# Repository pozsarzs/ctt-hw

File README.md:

**CTT - transistor tester and characteristic curve plotter**  
Copyright (C) 2010-2022 Pozsár Zsolt <pozsarzs@gmail.com>  
Homepage: <http://www.pozsarzs.hu/>  
GitHub: <https://github.com/pozsarzs/ctt-hw>

**Documentation**

- version:             1.0
- language:            en
- licence:             CC-BY-NC-4.0

**Hardware**

 - version:            v120128

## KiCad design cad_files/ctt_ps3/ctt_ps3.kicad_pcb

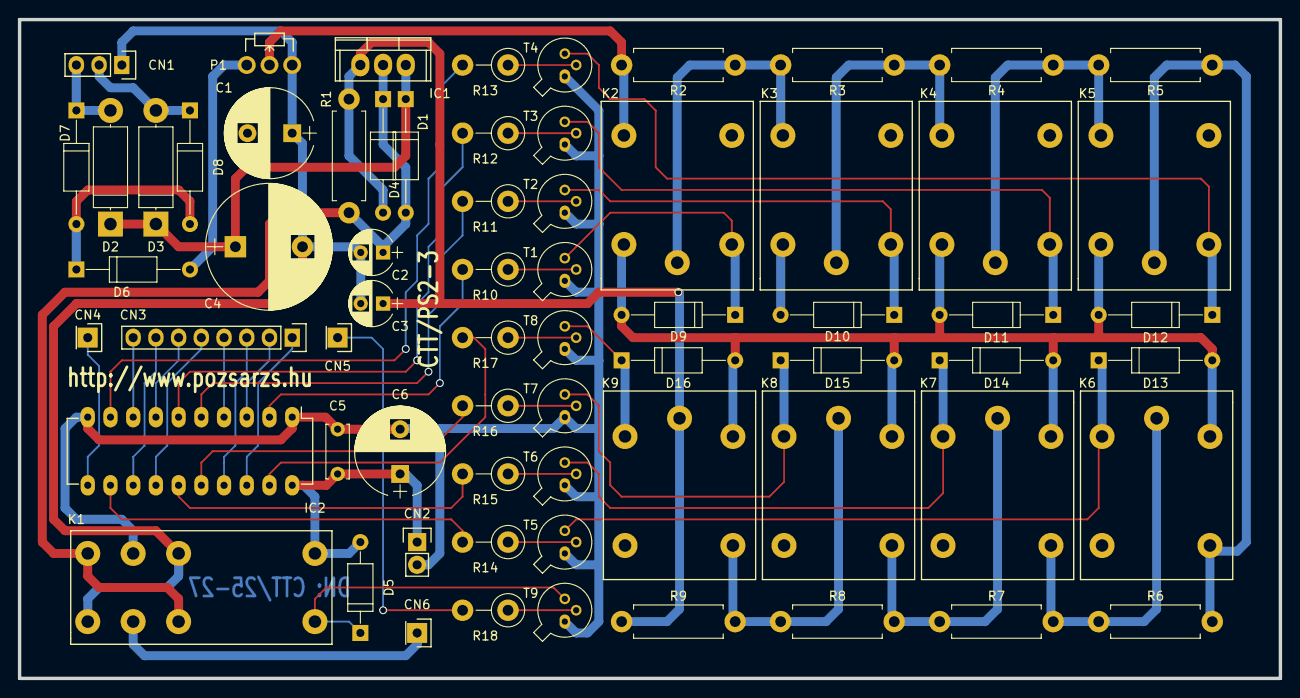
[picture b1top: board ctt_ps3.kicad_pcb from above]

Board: 2 copper layers, 141.0 x 73.7 mm, 67 parts (0 on the bottom side), 43 nets.

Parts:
C1: 2200u; CP_Radial_D14.0mm_P7.50mm
C2, C3: 10u; CP_Radial_D5.0mm_P2.50mm
C4: 470u; CP_Radial_D10.0mm_P5.00mm
C5: 100u; CP_Radial_D10.0mm_P5.00mm
C6: 100n; C_Disc_D6.0mm_W2.5mm_P5.00mm
CN1: Pin_Header_Straight_1x03
CN2: Pin_Header_Straight_1x02
CN3: Pin_Header_Straight_1x08
CN4, CN5, CN6: Pin_Header_Straight_1x01
D1, D4: 1N4002; D_A-405_P12.70mm_Horizontal
D2, D3: BY399; D_5W_P12.70mm_Horizontal
D5: 1N4001; D_A-405_P10.16mm_Horizontal
D6: ZPD27; D_A-405_P12.70mm_Horizontal
D7, D8, D9, D10, D11, D12, D13, D14, D15, D16: 1N4001; D_A-405_P12.70mm_Horizontal
IC1: LM317L; TO-220
IC2: 74LS374; DIP-20_W7.62mm_LongPads
K1: LMR2-5D; relay_lmr2
K2, K3, K4, K5, K6, K7, K8, K9: LEG-5; relay_leg
P1: 390; Potentiometer_WirePads_Small
R1: 640; R_Axial_DIN0411_L9.9mm_D3.6mm_P12.70mm_Horizontal
R2: 2; R_Axial_DIN0411_L9.9mm_D3.6mm_P12.70mm_Horizontal
R3: 4; R_Axial_DIN0411_L9.9mm_D3.6mm_P12.70mm_Horizontal
R4: 8; R_Axial_DIN0411_L9.9mm_D3.6mm_P12.70mm_Horizontal
R5: 16; R_Axial_DIN0411_L9.9mm_D3.6mm_P12.70mm_Horizontal
R6: 32; R_Axial_DIN0411_L9.9mm_D3.6mm_P12.70mm_Horizontal
R7: 64; R_Axial_DIN0411_L9.9mm_D3.6mm_P12.70mm_Horizontal
R8: 128; R_Axial_DIN0411_L9.9mm_D3.6mm_P12.70mm_Horizontal
R9: 256; R_Axial_DIN0411_L9.9mm_D3.6mm_P12.70mm_Horizontal
R10, R11, R12, R13, R14, R15, R16, R17, R18: 1k; R_Axial_DIN0411_L9.9mm_D3.6mm_P5.08mm_Vertical
T1, T2, T3, T4, T5, T6, T7, T8, T9: BC109; TO-18-3

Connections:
/5V 100mA AC: D2.2, D3.2, D7.1, D8.1
/5V 100mA AC COM: C1.2, C2.2, C3.2, C4.1, K1.3, K1.6, P1.1
GND: C5.2, C6.2, IC2.1, IC2.10, K1.4, T1.1, T2.1, T3.1, T4.1, T5.1, T6.1, T7.1, T8.1, T9.1
unnamed: C1.1, D1.1, D2.1, D3.1, IC1.3
unnamed: C2.1, D1.2, D4.1, IC1.2, K1.5, K1.8, R1.1
unnamed: C3.1, D4.2, IC1.1, K9.3, R1.2, R9.1
unnamed: C4.2, D6.1, D7.2, D8.2
unnamed: D5.2, K1.2, T9.3
unnamed: D6.2, P1.3
unnamed: D9.2, K2.2, T1.3
unnamed: D10.2, K3.2, T2.3
unnamed: D11.2, K4.2, T3.3
unnamed: D12.2, K5.2, T4.3
unnamed: D13.2, K6.2, T5.3
unnamed: D14.2, K7.2, T6.3
unnamed: D15.2, K8.2, T7.3
unnamed: D16.2, K9.2, T8.3
unnamed: IC2.2, R10.2
unnamed: IC2.5, R11.2
unnamed: IC2.6, R12.2
unnamed: IC2.9, R13.2
unnamed: IC2.12, R14.2
unnamed: IC2.15, R15.2
unnamed: IC2.16, R16.2
unnamed: IC2.19, R17.2
unnamed: K2.3, K3.4, R2.1, R3.2
unnamed: K2.4, P1.2, R2.2
unnamed: K3.3, K4.4, R3.1, R4.2
unnamed: K4.3, K5.4, R4.1, R5.2
unnamed: K5.3, K6.4, R5.1, R6.2
unnamed: K6.3, K7.4, R6.1, R7.2
unnamed: K7.3, K8.4, R7.1, R8.2
unnamed: K8.3, K9.4, R8.1, R9.2
unnamed: R10.1, T1.2
unnamed: R11.1, T2.2
unnamed: R12.1, T3.2
unnamed: R13.1, T4.2
unnamed: R14.1, T5.2
unnamed: R15.1, T6.2
unnamed: R16.1, T7.2
unnamed: R17.1, T8.2
unnamed: R18.1, T9.2
VCC: C5.1, C6.1, D5.1, D9.1, D10.1, D11.1, D12.1, D13.1, D14.1, D15.1, D16.1, IC2.20, K1.1, K2.1, K3.1, K4.1, K5.1, K6.1, K7.1, K8.1, K9.1

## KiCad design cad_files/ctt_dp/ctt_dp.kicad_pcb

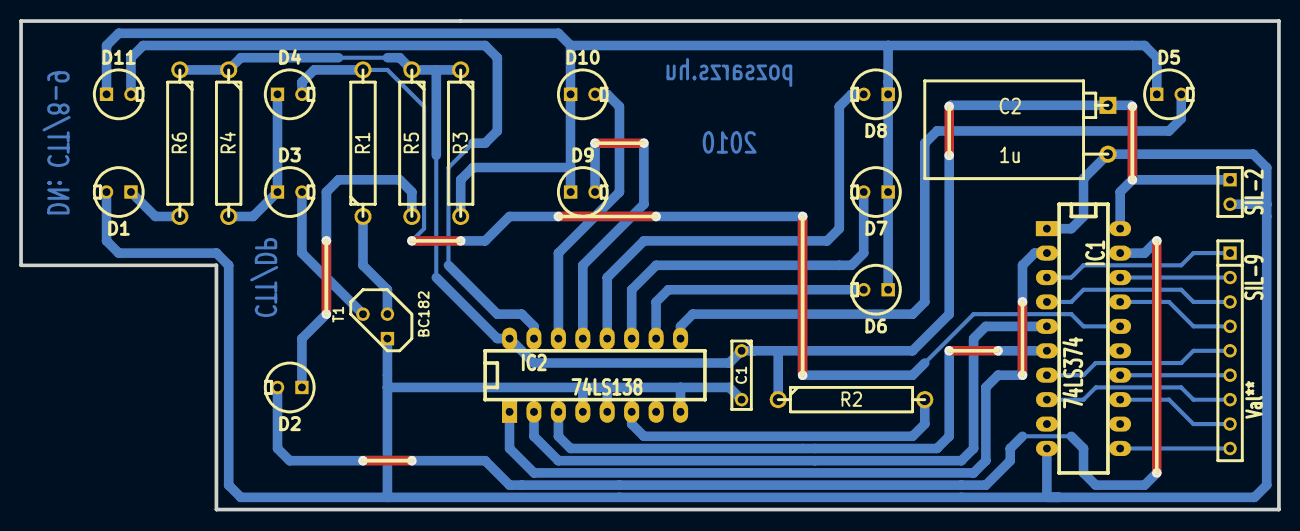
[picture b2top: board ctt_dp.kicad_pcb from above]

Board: 2 copper layers, 130.8 x 50.8 mm, 24 parts (0 on the bottom side), 21 nets.

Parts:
C1: 33n; C2
C2: 1u; CPR10X16
D1, D2, D3, D4, D5, D6, D7, D8, D9, D10, D11: LED; LEDV
IC1: 74LS374; 20DIP-ELL300
IC2: 74LS138; 16DIP-ELL300
R1, R2: 1k; R6
R3, R4, R5, R6: 330; R6
SIL-2: Val**; SIL-2
SIL-9: Val**; SIL-9
T1: BC182; TO92

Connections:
+5V: C1.1, C2.1, IC1.20, IC2.16, R2.1, R3.1, R4.1, R5.1, R6.1
GND: C1.2, C2.2, D1.2, IC1.1, IC1.10, IC2.4, IC2.5, IC2.8, T1.1
unnamed: D1.1, R6.2
unnamed: IC2.6, R2.2
unnamed: R1.1, T1.2
unnamed: D4.2, IC1.16, R1.2
unnamed: D2.1, R5.2
unnamed: IC1.5, IC2.2
unnamed: D5.1, D6.1, D7.1, D8.1, D9.1, D10.1, D11.1, R3.2
unnamed: D6.2, IC2.10
unnamed: D8.2, IC2.12
unnamed: D10.2, IC2.14
unnamed: D11.2, IC2.15
unnamed: D9.2, IC2.13
unnamed: D7.2, IC2.11
unnamed: D5.2, IC2.9
unnamed: IC1.2, IC2.1
unnamed: IC1.6, IC2.3
unnamed: D3.1, D4.1, R4.2
unnamed: D3.2, T1.3
unnamed: D2.2, IC1.19

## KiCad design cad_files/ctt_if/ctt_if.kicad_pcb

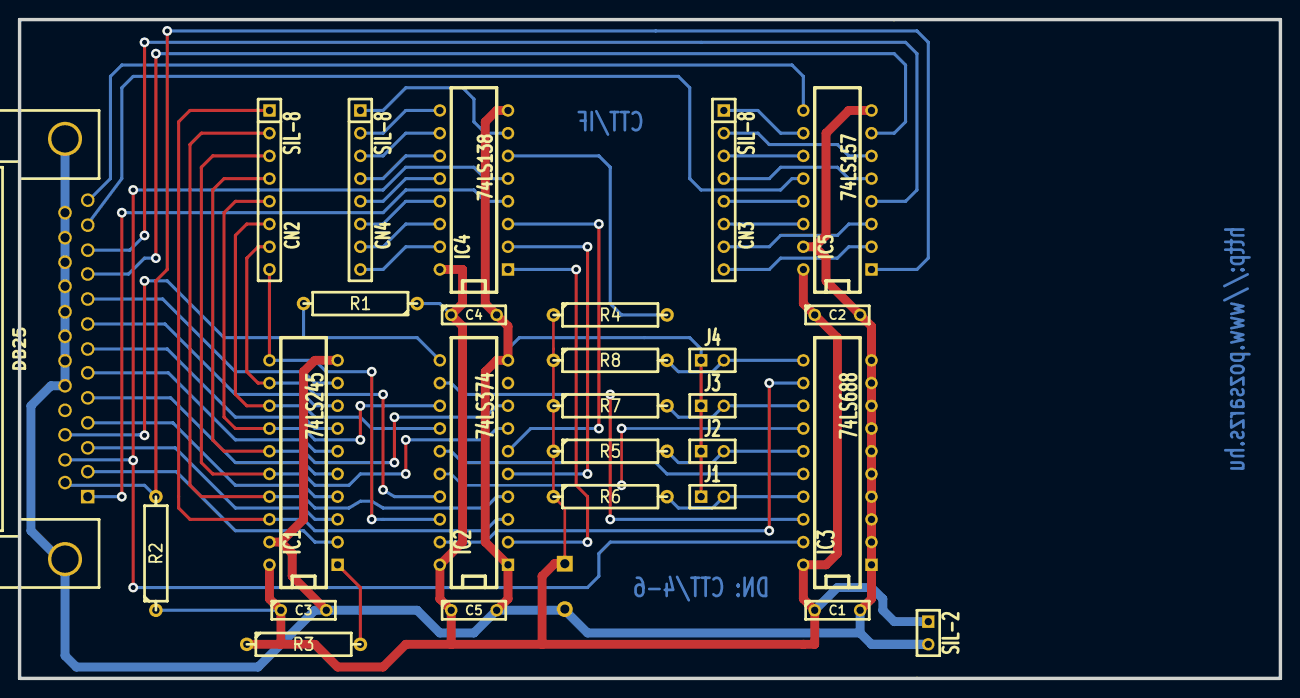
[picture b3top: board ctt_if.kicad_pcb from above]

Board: 2 copper layers, 141.0 x 73.7 mm, 28 parts (1 on the bottom side), 39 nets.

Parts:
C1, C2, C3, C4, C5: 33n; C2
C6: 100u; CPR10X16
CN1: DB25; DB25FC
IC1: 74LS245; 20dip300
IC2: 74LS374; 20dip300
IC3: 74LS688; 20dip300
IC4: 74LS138; 16dip300
IC5: 74LS157; 16dip300
J1, J2, J3, J4: JUMPER; SIL-2
R1, R2, R3, R4, R5, R6, R7, R8: 1k; R5
SIL-2: CN5; SIL-2
SIL-8: CN3; SIL-8
SIL-8#2: CN4; SIL-8
SIL-8#3: CN2; SIL-8

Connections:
/+5V: C1.1, C2.1, C3.1, C4.1, C5.1, C6.1, IC1.20, IC2.20, IC3.20, IC4.16, IC5.16, R1.1, R2.1, R3.1, R4.1, R5.1, R6.1, R7.1, R8.1
/DO0: IC1.18, IC2.3
/DO1: IC1.17, IC2.4
/DO2: IC1.16, IC2.7
/DO3: IC1.15, IC2.8
/DO4: IC1.14, IC2.13
/DO5: IC1.13, IC2.14
/DO6: IC1.12, IC2.17
/DO7: IC1.11, IC2.18
/GND: C1.2, C2.2, C3.2, C4.2, C5.2, C6.2, CN1.18, CN1.19, CN1.20, CN1.21, CN1.22, CN1.23, CN1.24, CN1.25, IC1.10, IC1.19, IC2.1, IC2.10, IC3.1, IC3.2, IC3.3, IC3.4, IC3.5, IC3.6, IC3.7, IC3.8, IC3.9, IC3.10, IC4.8, IC5.8, IC5.15, J1.1, J2.1, J3.1, J4.1
unnamed: IC3.11, J4.2, R8.2
unnamed: IC3.13, J3.2, R7.2
unnamed: IC3.15, J2.2, R5.2
unnamed: IC2.15, IC3.16
unnamed: IC2.19, IC3.12
unnamed: IC3.17, J1.2, R6.2
unnamed: CN1.1, IC4.4
unnamed: IC2.5, IC4.2
unnamed: CN1.2, IC1.2
unnamed: IC2.16, IC3.14
unnamed: IC2.12, IC3.18
unnamed: CN1.16, IC2.11, R1.2
unnamed: CN1.13, IC5.9
unnamed: CN1.14, IC5.1, R2.2
unnamed: CN1.15, IC3.19, IC4.5
unnamed: CN1.12, IC5.12
unnamed: IC1.1, R3.2
unnamed: CN1.11, IC5.4
unnamed: IC4.6, R4.2
unnamed: CN1.4, IC1.4
unnamed: CN1.6, IC1.6
unnamed: CN1.8, IC1.8
unnamed: IC2.6, IC4.3
unnamed: IC2.2, IC4.1
unnamed: CN1.10, IC5.7
unnamed: CN1.9, IC1.9
unnamed: CN1.7, IC1.7
unnamed: CN1.5, IC1.5
unnamed: CN1.3, IC1.3

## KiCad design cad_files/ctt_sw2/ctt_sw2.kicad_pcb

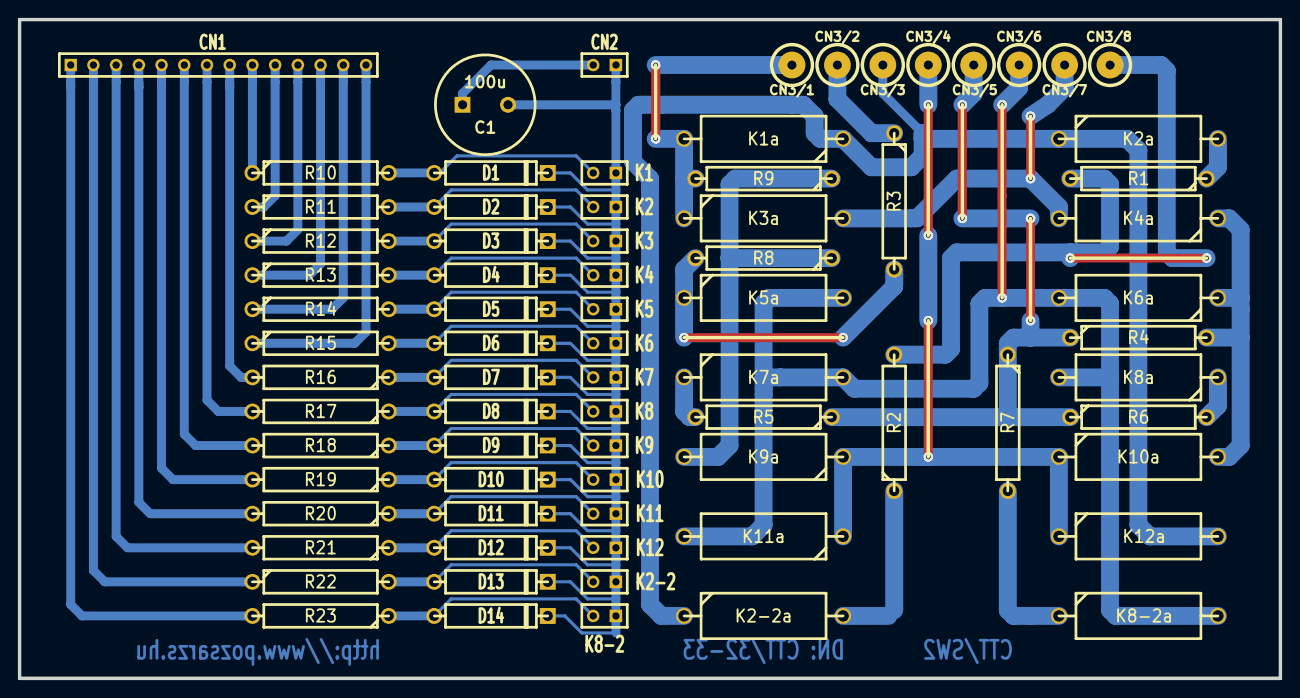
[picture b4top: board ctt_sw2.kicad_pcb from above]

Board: 2 copper layers, 141.0 x 73.7 mm, 76 parts (0 on the bottom side), 30 nets.

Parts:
1PIN: CN3/8; 1pin3
1PIN#2: CN3/7; 1pin3
1PIN#3: CN3/6; 1pin3
1PIN#4: CN3/1; 1pin3
1PIN#5: CN3/2; 1pin3
1PIN#6: CN3/3; 1pin3
1PIN#7: CN3/4; 1pin3
1PIN#8: CN3/5; 1pin3
C1: 100u; C2V10
D1, D2, D3, D4, D5, D6, D7, D8, D9, D10, D11, D12, D13, D14: 1N4148; D5
K1, K2, K2-2, K3, K4, K5, K6, K7, K8, K8-2, K9, K10, K11, K12: Reed_relay; SIL-2
K1a, K2-2a, K2a, K3a, K4a, K5a, K6a, K7a, K8-2a, K8a, K9a, K10a, K11a, K12a: SPST; R7
R1, R5: 100_1%; R6
R2, R10, R11, R12, R13, R14, R15, R16, R17, R18, R19, R20, R21, R22, R23: R; R6
R3: 33K; R6
R4: 1k_1%; R6
R6: 1_1%_1W; R6
R7: ?_1%_1W; R6
R8: 900K_1%; R6
R9: 100k_1%; R6
SIL-2: CN2; SIL-2
SIL-14: CN1; SIL-14

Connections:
0-1V_1: R1.2, R2.2
0-20V_1: R4.1, R5.1, R6.1, R7.1
+5V_1: C1.1, D1.2, D2.2, D3.2, D4.2, D5.2, D6.2, D7.2, D8.2, D9.2, D10.2, D11.2, D12.2, D13.2, D14.2, K1.1, K2.1, K2-2.1, K3.1, K4.1, K5.1, K6.1, K7.1, K8.1, K8-2.1, K9.1, K10.1, K11.1, K12.1
Base_1: K1a.1, K2-2a.1, K2a.1, K12a.2
COM_1: K1a.2, K3a.1, R9.2
Collector_1: K5a.2, K6a.2, K7a.2, K8-2a.2, K8a.2, K11a.2
Emitter_1: K3a.2, K4a.2
unnamed: D12.1, K12.2, R21.1
unnamed: D11.1, K11.2, R20.1
unnamed: D10.1, K10.2, R19.1
unnamed: D9.1, K9.2, R18.1
unnamed: D7.1, K7.2, R16.1
unnamed: D3.1, K3.2, R12.2
unnamed: D4.1, K4.2, R13.2
unnamed: D5.1, K5.2, R14.2
unnamed: D2.1, K2.2, R11.2
unnamed: K2-2a.2, R2.1
unnamed: K4a.1, K6a.1, K10a.2, R4.2
unnamed: K7a.1, R5.2
unnamed: K8-2a.1, R7.2
unnamed: K8a.1, R6.2
unnamed: K5a.1, R3.2, R8.2
unnamed: K2a.2, R1.1
unnamed: K9a.2, R8.1, R9.1
unnamed: D1.1, K1.2, R10.2
unnamed: D13.1, K2-2.2, R22.2
unnamed: D6.1, K6.2, R15.2
unnamed: D14.1, K8-2.2, R23.1
unnamed: D8.1, K8.2, R17.1
Um_1: K9a.1, K10a.1, K11a.1, K12a.1

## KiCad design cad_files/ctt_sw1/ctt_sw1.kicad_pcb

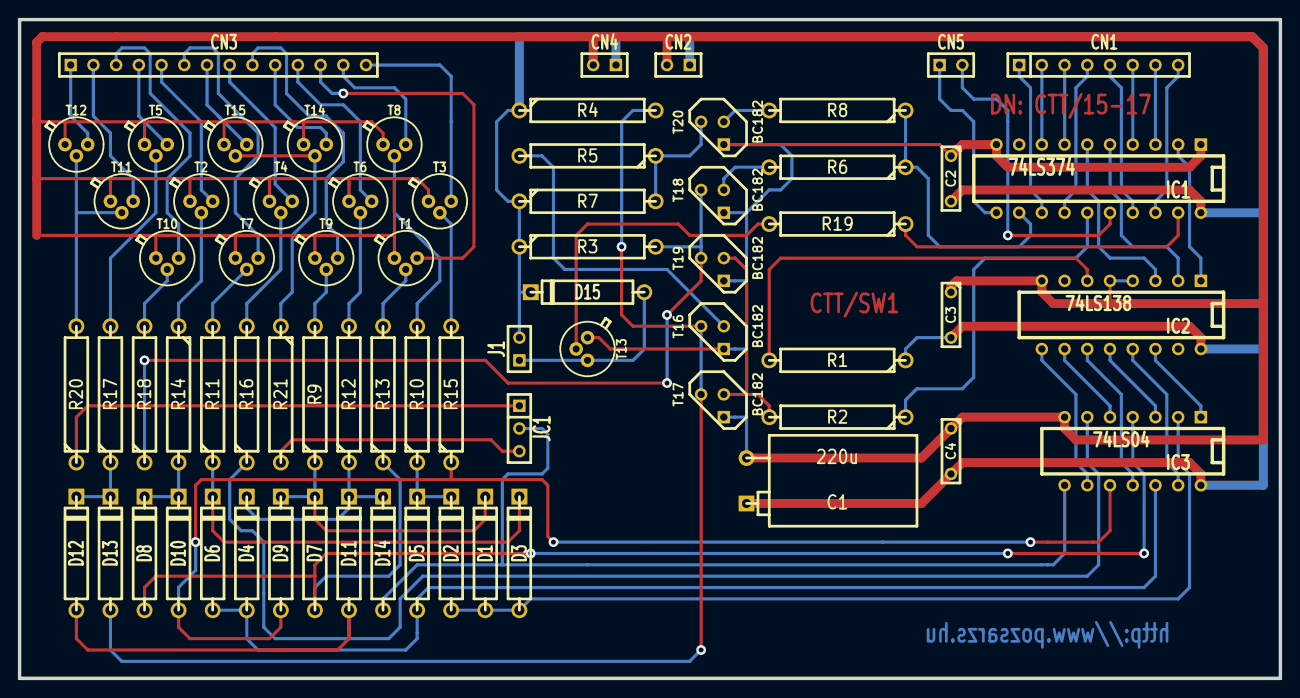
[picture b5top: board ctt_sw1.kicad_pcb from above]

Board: 2 copper layers, 141.0 x 73.7 mm, 70 parts (0 on the bottom side), 50 nets.

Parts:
C1: 220u; CPR10X16
C2, C3, C4: 100n; C2
D1, D2, D3, D4, D5, D6, D7, D8, D9, D10, D11, D12, D13, D14, D15: 1N4148; D5
IC1: 74LS374; DIP-20__300
IC2: 74LS138; DIP-16__300
IC3: 74LS04; DIP-14__300
J1: Reed_relay; SIL-2
JC1: SWITCH_INV; SIL-3
R1, R2, R3, R4, R5, R6, R7, R8, R9, R10, R11, R12, R13, R14, R15, R16, R17, R18, R19, R20, R21: 1k; R6
SIL-2: CN4; SIL-2
SIL-2#2: CN5; SIL-2
SIL-2#3: CN2; SIL-2
SIL-8: CN1; SIL-8
SIL-14: CN3; SIL-14
T1, T2, T3, T4, T5, T6, T7, T8, T9, T10, T11, T12, T13, T14, T15: BC109C; TO18EBC
T16, T17, T18, T19, T20: BC182; TO92

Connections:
/+5V: C1.1, C2.2, C3.2, C4.2, D15.2, IC1.20, IC2.16, IC3.14, J1.2, R1.1, R3.1, R4.1, R7.1
GND: C1.2, C2.1, C3.1, C4.1, IC1.1, IC1.10, IC2.4, IC2.5, IC2.8, IC3.7, T1.1, T2.1, T3.1, T4.1, T5.1, T6.1, T7.1, T8.1, T9.1, T10.1, T11.1, T12.1, T13.1, T14.1, T15.1, T16.1, T17.1, T18.1, T19.1, T20.1
unnamed: D13.1, R4.2, T16.3, T17.3
unnamed: R3.2, R18.1, T18.3, T19.3
unnamed: R2.2, T17.2, T19.2
unnamed: D1.2, D7.2, D9.2, R9.1
unnamed: D4.2, D11.2, D14.2, R12.1
unnamed: R20.2, T11.2, T12.2
unnamed: D1.1, D2.1, D3.1, IC3.2
unnamed: D4.1, D5.1, D6.1, IC3.12
unnamed: D3.2, D6.2, R11.1
unnamed: IC1.19, R19.1
unnamed: R19.2, T13.2
unnamed: JC1.3, R21.2
unnamed: JC1.1, R20.1
unnamed: R15.2, T3.2
unnamed: R14.1, T2.2
unnamed: IC1.15, R2.1
unnamed: R8.2, T20.2
unnamed: IC1.12, R6.1, R8.1
unnamed: R6.2, T18.2
unnamed: R5.2, T16.2
unnamed: R13.2, T1.2
unnamed: R12.2, T6.2
unnamed: R10.2, T8.2
unnamed: R9.2, T9.2
unnamed: IC2.9, IC3.9
unnamed: IC2.11, IC3.11
unnamed: IC2.12, IC3.3
unnamed: IC2.13, IC3.13
unnamed: IC2.6, R1.2
unnamed: IC2.10, IC3.5
unnamed: D14.1, IC3.8, JC1.2
unnamed: IC2.14, IC3.1
unnamed: R17.2, T5.2
unnamed: R21.1, T14.2, T15.2
unnamed: R11.2, T7.2
unnamed: R16.2, T4.2
unnamed: IC1.2, IC2.1
unnamed: IC1.5, IC2.2
unnamed: IC1.6, IC2.3
unnamed: R18.2, T10.2
unnamed: D15.1, J1.1, T13.3
unnamed: R5.1, R7.2, T20.3
unnamed: D2.2, D5.2, R10.1
unnamed: D8.2, D10.2, R14.2
unnamed: D12.2, D13.2, R17.1
unnamed: D7.1, D8.1, IC3.4, R13.1
unnamed: D9.1, D10.1, IC3.10, R15.1
unnamed: D11.1, D12.1, IC3.6, R16.1

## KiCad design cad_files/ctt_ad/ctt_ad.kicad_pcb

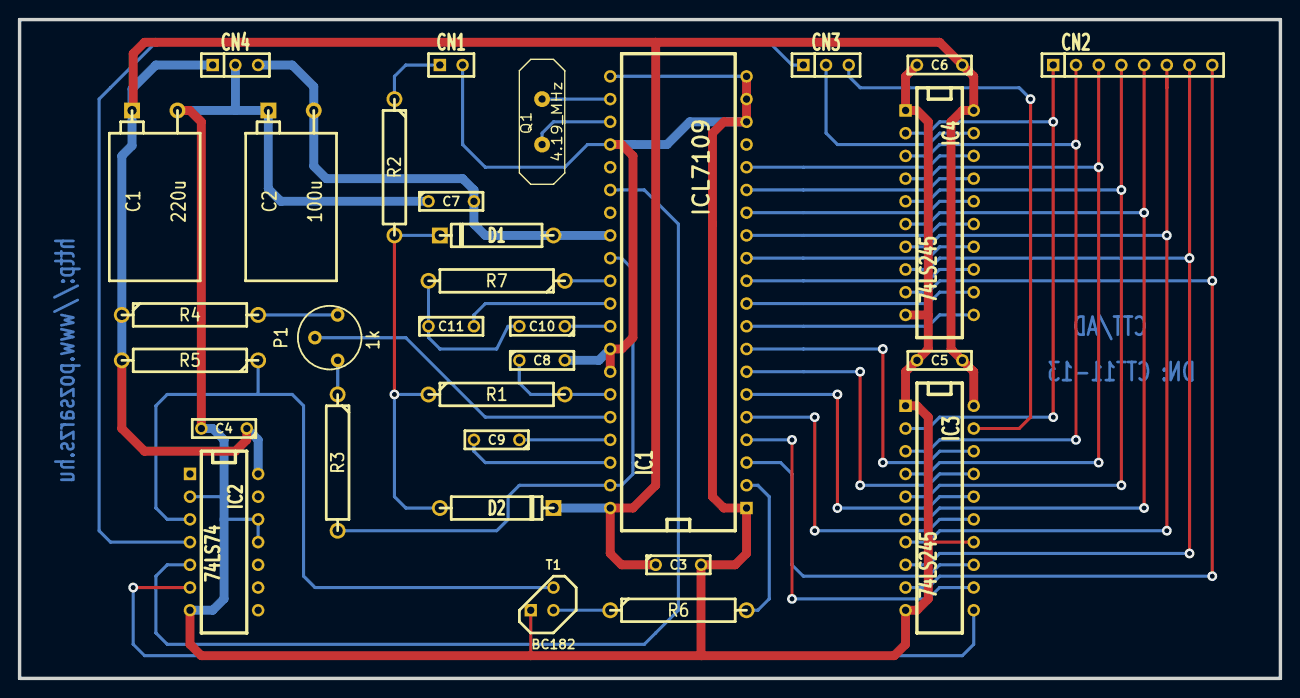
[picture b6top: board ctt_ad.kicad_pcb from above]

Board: 2 copper layers, 141.0 x 73.7 mm, 31 parts (0 on the bottom side), 44 nets.

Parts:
C1: 220u; CPR10X16
C2: 100u; CPR10X16
C3, C4, C5, C6, C7, C10: 100n; C2
C8: 10n; C2
C9: 1u; C2
C11: 150n; C2
CN1: Val**; SIL-2
CN2: Val**; SIL-8
CN3, CN4: Val**; SIL-3
D1, D2: 1N4148; D5
IC1: ICL7109; 40dip600
IC2: 74LS74; 14dip300
IC3, IC4: 74LS245; 20dip300
P1: 1k; RV2
Q1: 4.19_MHz; HC-18UV
R1: 1M; R6
R2: 10k; R6
R3: 22k; R6
R4: 3.9k; R6
R5, R6: 1k; R6
R7: 82k; R6
T1: BC182; TO92

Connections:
+5V: C1.1, C3.1, C4.1, C5.1, C6.1, D2.2, IC1.40, IC2.14, IC3.20, IC4.20, R4.1, R5.2
-5VA: C2.2, C7.2, D1.1, IC1.28
DI0_1: IC3.2, IC4.2
DI1_1: IC3.3, IC4.3
DI2_1: IC3.4, IC4.4
DI3_1: IC3.5, IC4.5
DI4_1: IC3.6, IC4.6
DI5_1: IC3.7, IC4.7
DI6_1: IC3.8, IC4.8
DI7_1: IC3.9, IC4.9
GND: C1.2, C2.1, C3.2, C4.2, C5.2, C6.2, C7.1, C8.2, IC1.1, IC1.18, IC1.19, IC1.20, IC1.24, IC1.33, IC1.34, IC2.2, IC2.7, IC3.10, IC3.14, IC4.10, T1.1
unnamed: R6.1, T1.2
unnamed: IC2.3, R5.1, T1.3
unnamed: IC1.3, IC3.13
unnamed: IC1.2, R6.2
unnamed: C9.2, IC1.38
unnamed: IC1.23, Q1.1
unnamed: P1.3, R4.2
unnamed: D1.2, D2.1, R1.1, R2.2
unnamed: IC1.29, IC1.39, R3.2
unnamed: C11.2, IC1.31
unnamed: IC1.30, R7.1
unnamed: IC1.10, IC4.12
unnamed: IC1.12, IC4.14
unnamed: IC1.14, IC4.16
unnamed: IC1.16, IC4.18
unnamed: IC1.8, IC3.18
unnamed: IC1.6, IC3.16
unnamed: IC1.7, IC3.17
unnamed: IC1.5, IC3.15
unnamed: IC1.9, IC4.11
unnamed: IC1.15, IC4.17
unnamed: IC1.13, IC4.15
unnamed: IC1.11, IC4.13
unnamed: IC3.1, IC4.1
unnamed: C10.1, IC1.32
unnamed: C10.2, C11.1, R7.2
unnamed: IC1.35, R1.2
unnamed: P1.1, R3.1
unnamed: IC1.36, P1.2
unnamed: C9.1, IC1.37
unnamed: IC1.26, IC2.5
unnamed: IC1.4, IC3.12
unnamed: IC2.6, IC3.11

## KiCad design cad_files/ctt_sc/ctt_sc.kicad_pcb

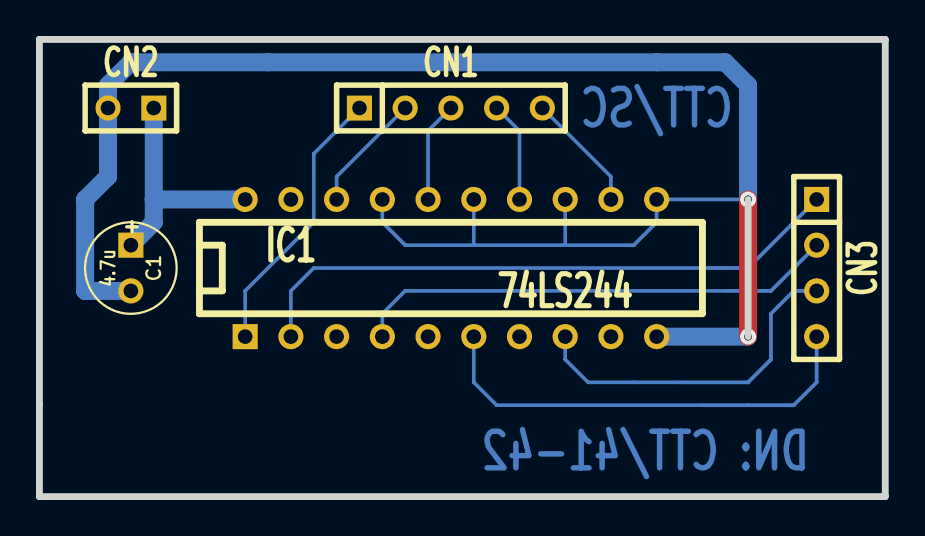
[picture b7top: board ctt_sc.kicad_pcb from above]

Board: 2 copper layers, 47.0 x 25.4 mm, 5 parts (0 on the bottom side), 2 nets.

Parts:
C1: 4.7u; C1V5
IC1: 74LS244; DIP-20__300
SIL-2: CN2; SIL-2
SIL-4: CN3; SIL-4
SIL-5: CN1; SIL-5

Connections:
/GND: C1.2, IC1.10, IC1.11, IC1.13, IC1.15, IC1.17
VCC: C1.1, IC1.20

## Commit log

2011-03-27 Struktura importalasa
2011-03-27 Mar kesz fajlok beimportalasa
2011-03-27 2011. 03. 27. délutáni állapot
2011-04-02 2011. 04. 02. reggeli állapot
2011-04-02 2011. 04. 02. délelőtti állapot
2011-04-10 2011. 04. 10-i állapot
2011-04-14 2011.04.14-i állapot.
2011-04-18 2011.04.18-i állapot.
2011-04-18 2011.04.18.esti állapot.
2011-04-20 2011.04.20-i állapot.
2011-05-01 2011. 05. 01-i állapot.
2011-05-07 2011. 05. 07-i állapot.
2011-05-08 2011. 05. 08-i állapot.
2011-05-10 2011. 05. 10-i állapot.
2011-05-12 2011. 05. 12-i állapot.
2011-05-14 2011. 05. 14. 16.16 állapot.
2011-05-14 2011. 05. 14. esti állapot.
2011-05-15 2011. 05. 15. du.-i állapot.
2011-05-15 2011. 05. 15. esti állapot.
2011-05-17 2011.04.16-i állapot.
2011-05-17 2011.04.16. esti állapot.
2011-05-19 2011.05.19-i állapot.
2011-05-22 2011.05.22-i állapot.
2011-05-22 2011.05.22.esti állapot.
2011-05-26 2011.05.26.esti állapot.
2011-05-28 2011.05.28-i állapot.
2011-05-28 2011.05.28. esti állapot.
2011-06-04 2011.06.04-i állapot.
2011-06-04 2011.06.04-i állapot. #2
2011-06-05 2011.06.05-i állapot.
2011-06-05 2011.06.05-i állapot. #2
2011-06-05 2011.06.05. esti állapot.
2011-06-07 2011.06.07-i állapot.
2011-06-07 2011.06.07. esti állapot.
2011-06-07 2011.06.07. esti állapot. #2
2011-06-11 2011.06.11-i állapot.
2011-07-29 07.28-i állapot.
2011-08-07 08.07-i állapot.
2011-08-09 08.09-i állapot
2011-08-09 08.10. hajnali állapot
2011-08-13 2011. 08. 13. de.-i állapot.
2012-01-08 2012.01.08-i állapot.
2012-01-08 2012.01.08. 2. feltöltés.
2012-01-08 2012.01.08. 3. feltöltés.
2012-01-19 2012.01.19-i feltöltés.
2012-01-19 2012.01.19-i 2. feltöltés.
2012-01-19 2012.01.19-i 3. feltöltés.
2012-01-28 2012.01.28-i feltöltés. Új faszerkezet.
2012-01-28 2012.01.28-i 2. feltöltés.
2022-09-01 220901
2022-09-02 220902
2022-09-03 220903
2022-09-04 220904
2022-09-05 220905
2022-09-07 220907
2022-09-09 220909
2022-09-10 220910
2022-09-11 220911
2022-09-12 220912
2022-09-14 220914
2022-09-15 220915
2022-09-17 220917
2022-09-18 220918
2022-09-19 220919
2022-09-20 220920
2022-09-26 220926
2022-09-28 220928
2022-10-06 221006
2023-01-02 230102
